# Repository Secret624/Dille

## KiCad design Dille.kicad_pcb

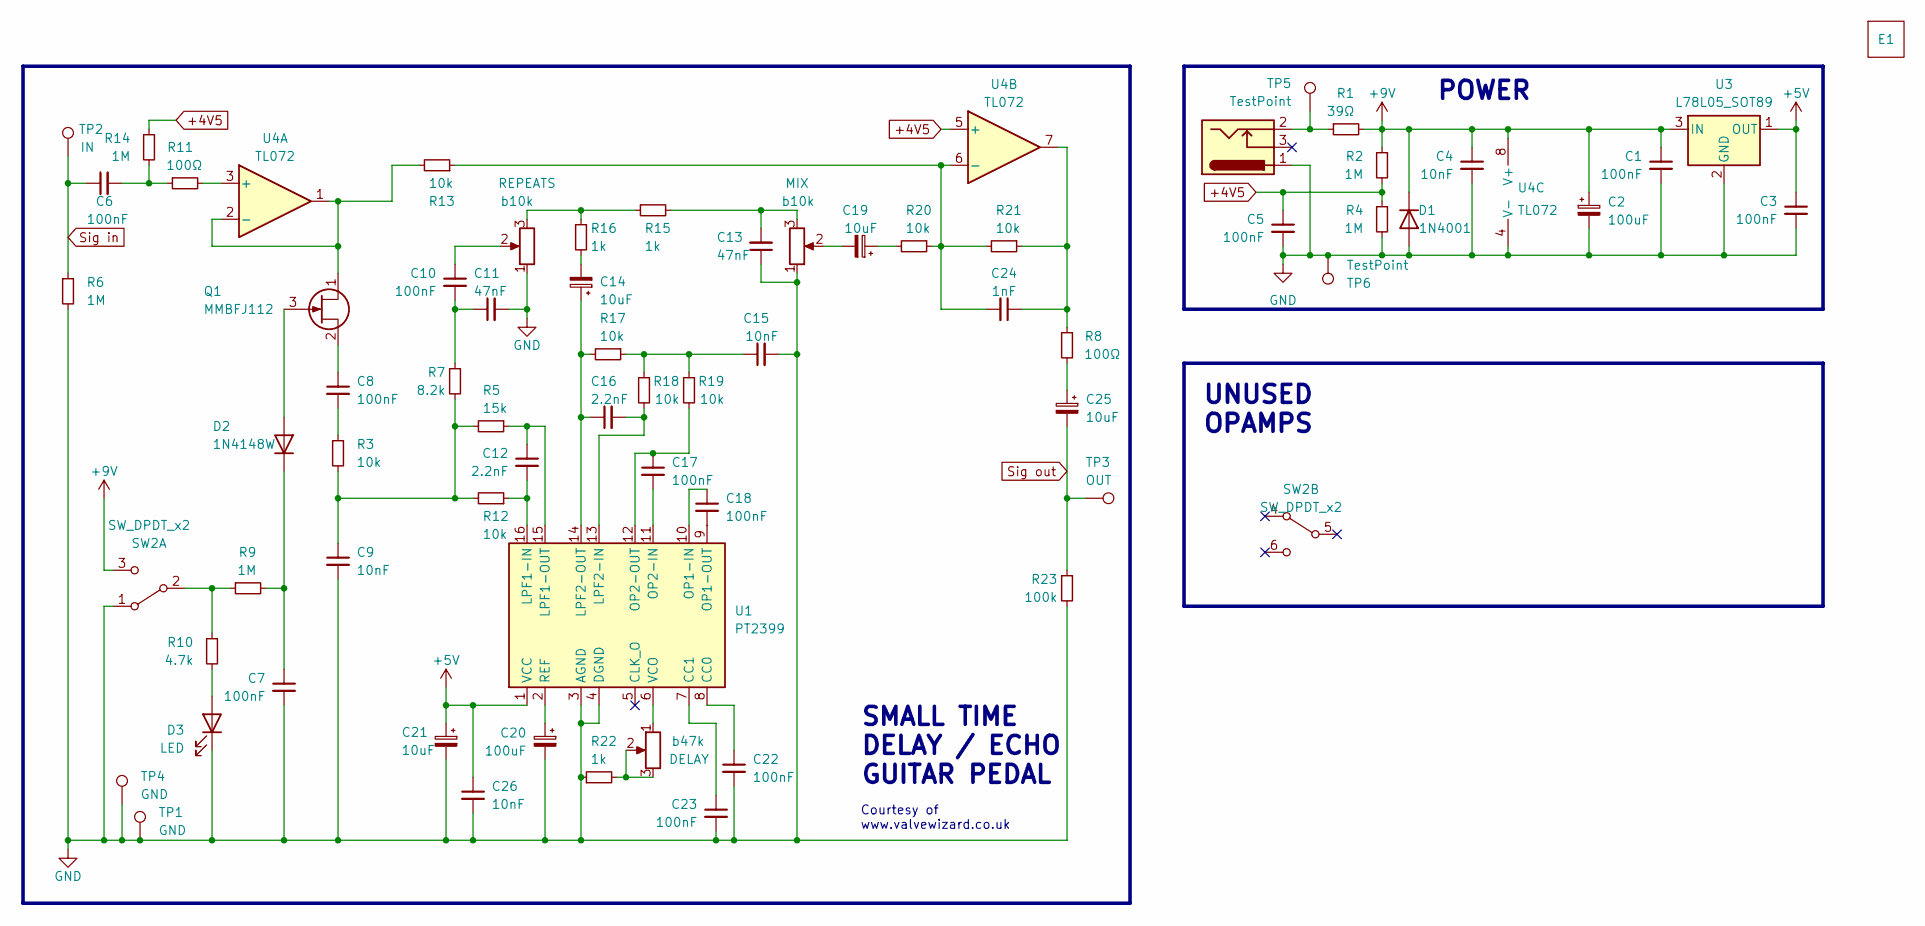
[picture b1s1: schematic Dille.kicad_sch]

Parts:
C1, C3, C5, C6, C7, C8, C10, C17, C18, C22, C23: 100nF; C_0805_2012Metric_Pad1.18x1.45mm_HandSolder; LCSC# C282730
C2, C20: 100uF; CP_Elec_6.3x4.5; LCSC# C5374787
C4, C9, C15, C26: 10nF; C_0805_2012Metric_Pad1.18x1.45mm_HandSolder; LCSC# C58456
C11, C13: 47nF; C_0805_2012Metric_Pad1.18x1.45mm_HandSolder; LCSC# C282770
C12, C16: 2.2nF; C_0805_2012Metric_Pad1.18x1.45mm_HandSolder; LCSC# C5137580
C14, C19, C21, C25: 10uF; CP_Elec_4x4.5; LCSC# C249787
C24: 1nF; C_0805_2012Metric_Pad1.18x1.45mm_HandSolder; LCSC# C713510
D1: 1N4001; D_SOD-123F; LCSC# C2892326
D2: 1N4148W; D_SOD-123; LCSC# C5345962
D3: LED; LED_D3.0mm
E1: 1590B
J1: Barrel_Jack_Switch; BarrelJack_Kycon_KLDX-0202-xC_Horizontal
Q1: MMBFJ112; SOT-23; LCSC# C258195
R1: 39Ω; R_1206_3216Metric_Pad1.30x1.75mm_HandSolder; LCSC# C153384
R2, R4, R6, R9, R14: 1M; R_0805_2012Metric_Pad1.20x1.40mm_HandSolder; LCSC# C103906
R3, R12, R13, R17, R18, R19, R20, R21: 10k; R_0805_2012Metric_Pad1.20x1.40mm_HandSolder; LCSC# C17414
R5: 15k; R_0805_2012Metric_Pad1.20x1.40mm_HandSolder; LCSC# C2933528
R7: 8.2k; R_0805_2012Metric_Pad1.20x1.40mm_HandSolder; LCSC# C2907342
R8, R11: 100Ω; R_0805_2012Metric_Pad1.20x1.40mm_HandSolder; LCSC# C3016626
R10: 4.7k; R_0805_2012Metric_Pad1.20x1.40mm_HandSolder; LCSC# C2907326
R15, R16, R22: 1k; R_0805_2012Metric_Pad1.20x1.40mm_HandSolder; LCSC# C2907232
R23: 100k; R_0805_2012Metric_Pad1.20x1.40mm_HandSolder; LCSC# C2907293
RV1, RV2: b10k; UT right angle long pin
RV3: b47k; UT right angle long pin
SW2: SW_DPDT_x2; Ural dpdt
TP1, TP4: GND; Test point 2.5x1.5
TP2: IN; Test point 2.5x1.5
TP3: OUT; Test point 2.5x1.5
TP5, TP6: TestPoint; TestPoint_Pad_4.0x4.0mm
U1: PT2399; SOP-16_3.9x9.9mm_P1.27mm; LCSC# C126407
U3: L78L05_SOT89; SOT-89-3; LCSC# C5181466
U4: TL072; SO-8_3.9x4.9mm_P1.27mm

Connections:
+4V5: C5.1, R2.2, R4.1, R14.1, U4.5 (+)
+5V: C3.1, C21.1, C26.1, U1.1 (VCC), U3.1 (OUT)
+9V: C1.1, C2.1, C4.1, D1.1 (K), R1.2, R2.1, SW2.3 (C), U3.3 (IN), U4.8 (V+)
GND: C1.2, C2.2, C3.2, C4.2, C5.2, C7.2, C9.2, C11.2, C13.1, C15.2, C20.2, C21.2, C22.2, C23.2, C26.2, D1.2 (A), D3.1 (K), J1.1, R4.2, R6.2, R22.1, R23.2, RV1.1, RV2.1, SW2.1 (A), TP1.1, TP4.1, TP6.1, U1.3 (AGND), U1.4 (DGND), U3.2 (GND), U4.4 (V-); also elsewhere on the board
unnamed: C6.2, R11.1, R14.2
unnamed: C8.2, R3.1
unnamed: C9.1, R3.2, R5.2, R7.2, R12.2
unnamed: C10.1, RV1.2
unnamed: C10.2, C11.1, R7.1
unnamed: C13.2, R15.2, RV2.3
unnamed: C14.2, R16.2
unnamed: C15.1, R17.1, R18.1, R19.1
unnamed: C19.1, R20.2
unnamed: C19.2, RV2.2
unnamed: C24.1, R8.1, R21.1, U4.7
unnamed: C25.1, R8.2
unnamed: D2.2 (A), Q1.3 (G)
unnamed: C7.1, D2.1 (K), R9.2
unnamed: D3.2 (A), R10.2
unnamed 19: J1.2, R1.1, TP5.1; also elsewhere on the board
unnamed: Q1.1 (D), R13.2, U4.1, U4.2 (-)
unnamed: C8.1, Q1.2 (S)
unnamed: R15.1, R16.1, RV1.3
unnamed: R22.2, RV3.2, RV3.3
unnamed: R9.1, R10.1, SW2.2 (B)
unnamed: C22.1, U1.8 (CC0)
unnamed: C23.1, U1.7 (CC1)
unnamed: C12.2, R12.1, U1.16 (LPF1-IN)
unnamed: C12.1, R5.1, U1.15 (LPF1-OUT)
unnamed: C16.2, R18.2, U1.13 (LPF2-IN)
unnamed: C14.1, C16.1, R17.2, U1.14 (LPF2-OUT)
unnamed: C18.1, U1.10 (OP1-IN)
unnamed: C18.2, U1.9 (OP1-OUT)
unnamed: C17.2, U1.11 (OP2-IN)
unnamed: C17.1, R19.2, U1.12 (OP2-OUT)
unnamed: C20.1, U1.2 (REF)
unnamed: RV3.1, U1.6 (VCO)
unnamed: R11.2, U4.3 (+)
unnamed: C24.2, R13.1, R20.1, R21.2, U4.6 (-)
Sig in: C6.1, R6.1, TP2.1
Sig out: C25.2, R23.1, TP3.1

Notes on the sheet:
Courtesy of www.valvewizard.co.uk
UNUSED OPAMPS
POWER
SMALL TIME DELAY / ECHO GUITAR PEDAL

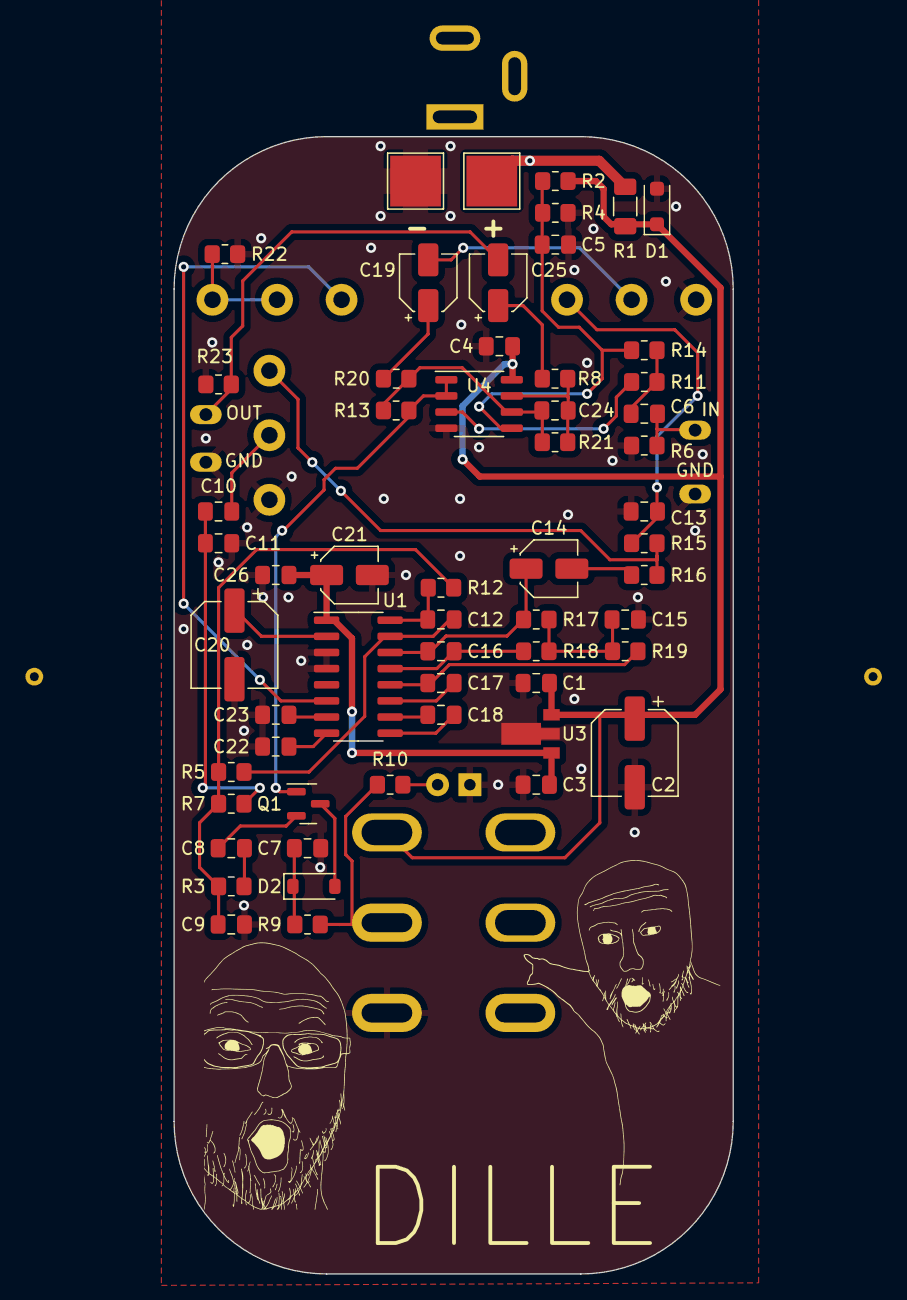
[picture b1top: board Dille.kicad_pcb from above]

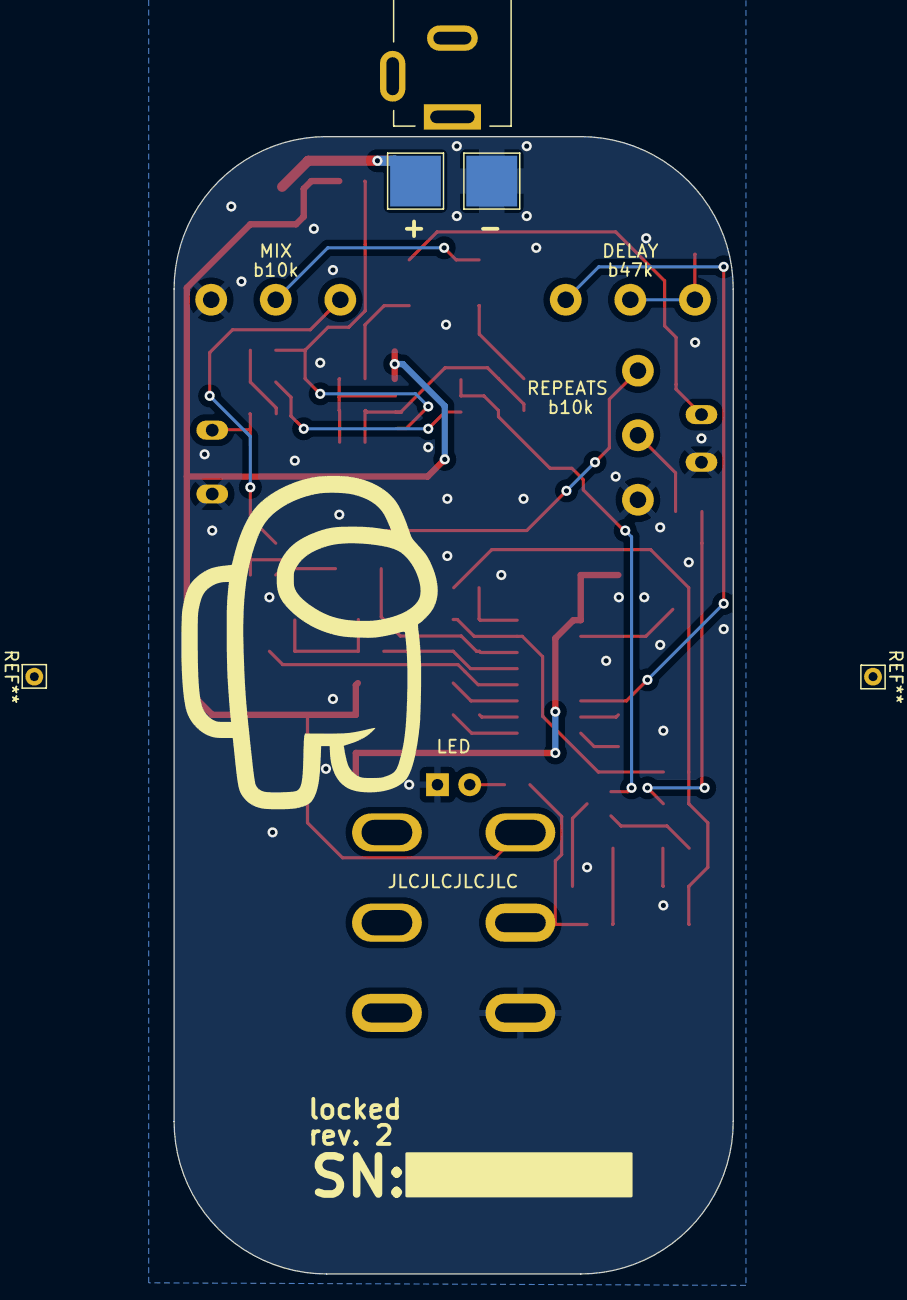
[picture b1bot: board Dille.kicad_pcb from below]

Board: 2 copper layers, 44.0 x 89.5 mm, 70 parts (9 on the bottom side), 41 nets.

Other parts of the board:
TP5#2, TP6#2: TestPoint; TestPoint_Pad_4.0x4.0mm

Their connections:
GND: TP6#2.1; also elsewhere on the board
unnamed 19: TP5#2.1; also elsewhere on the board

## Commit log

2023-11-05 pcb 2
2023-11-05 Saddamointi
2023-11-18 Added gerbers
2023-12-14 Rev 2
2023-12-15 Silkscreen updated
2023-12-21 Revision 2
